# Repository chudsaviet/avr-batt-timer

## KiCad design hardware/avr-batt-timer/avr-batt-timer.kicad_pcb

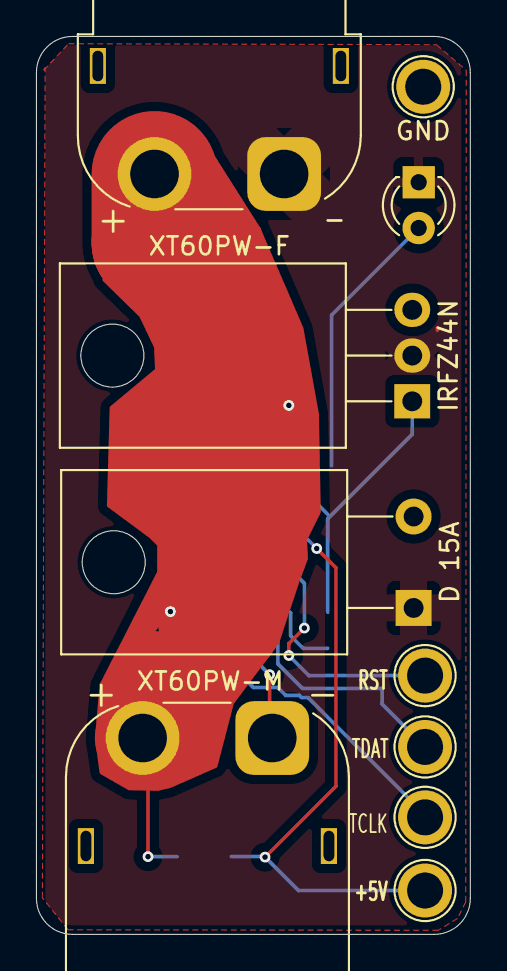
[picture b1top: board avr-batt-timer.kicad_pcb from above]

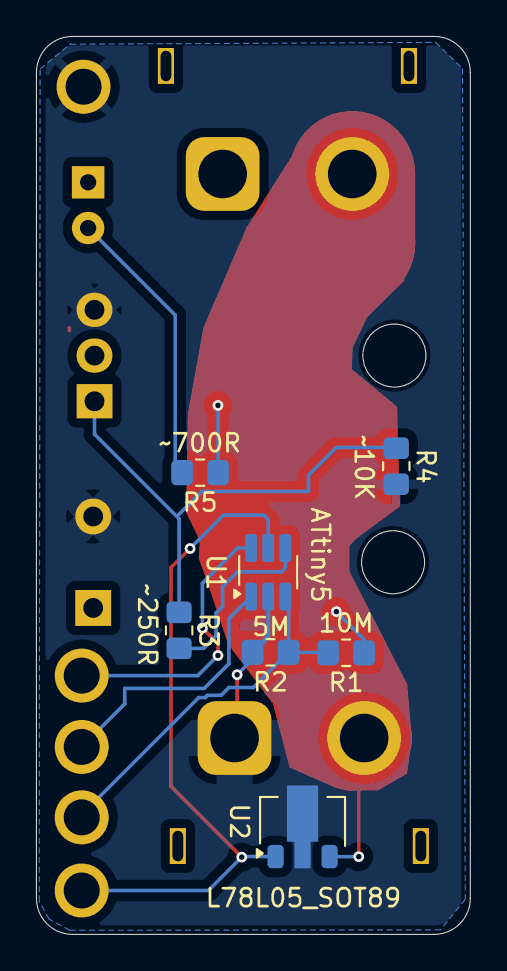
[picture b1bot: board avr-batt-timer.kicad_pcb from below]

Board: 2 copper layers, 24.1 x 49.9 mm, 17 parts (7 on the bottom side), 10 nets.

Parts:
D1: LED; LED_D3.0mm
D2: D 15A; TO-220-2_Horizontal_TabDown
J1: XT60PW-M; AMASS_XT60PW-M_1x02_P7.20mm_Horizontal
J2: XT60PW-F; AMASS_XT60PW-F_1x02_P7.20mm_Horizontal
MOSFET1: IRFZ44N; TO-220-3_Horizontal_TabDown
R1: 10M; R_0805_2012Metric_Pad1.20x1.40mm_HandSolder
R2: 5M; R_0805_2012Metric_Pad1.20x1.40mm_HandSolder
R3: ~250R; R_0805_2012Metric_Pad1.20x1.40mm_HandSolder
R4: ~10K; R_0805_2012Metric_Pad1.20x1.40mm_HandSolder
R5: ~700R; R_0805_2012Metric_Pad1.20x1.40mm_HandSolder
TP1: +5V; TestPoint_Plated_Hole_D2.0mm
TP2: RST; TestPoint_Plated_Hole_D2.0mm
TP3: TDAT; TestPoint_Plated_Hole_D2.0mm
TP4: TCLK; TestPoint_Plated_Hole_D2.0mm
TP5: GND; TestPoint_Plated_Hole_D2.0mm
U1: ATtiny5; SOT-23-6_Handsoldering
U2: L78L05_SOT89; SOT-89-3

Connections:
+5V: TP1.1, U1.5 (VCC), U2.1 (OUT)
GND: D2.2 (A), J1.1, MOSFET1.3 (S), R2.2, R4.2, TP5.1, U1.2 (GND), U2.2 (GND)
LOAD: D1.1 (K), D2.1 (K), J2.1, MOSFET1.2 (D)
unnamed: D1.2 (A), R5.2
unnamed: MOSFET1.1 (G), R3.1, R4.1
unnamed: R3.2, U1.4 (PB2)
RESET: TP2.1, U1.6 (~RESET/PB3)
TPICLK: R1.2, R2.1, TP4.1, U1.3 (PB1)
TPIDATA: TP3.1, U1.1 (PB0)
VDD: J1.2, J2.2, R1.1, R5.1, U2.3 (IN)

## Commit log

2024-12-18 Initial 'blinky' code.
2024-12-18 Added KiCad project.
2024-12-18 Initial schematic.
2024-12-21 Added most components.
2024-12-22 Added components. Initial PCB design.
2024-12-28 Supposingly working code.
2025-01-10 Fixed TPICLK pin connection. Replaced programming pins with holes.
2025-01-26 Last version with attiny5.
